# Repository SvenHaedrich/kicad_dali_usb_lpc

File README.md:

KiCad Project for DALI to USB interface based on NXP LPC 1114 µController.

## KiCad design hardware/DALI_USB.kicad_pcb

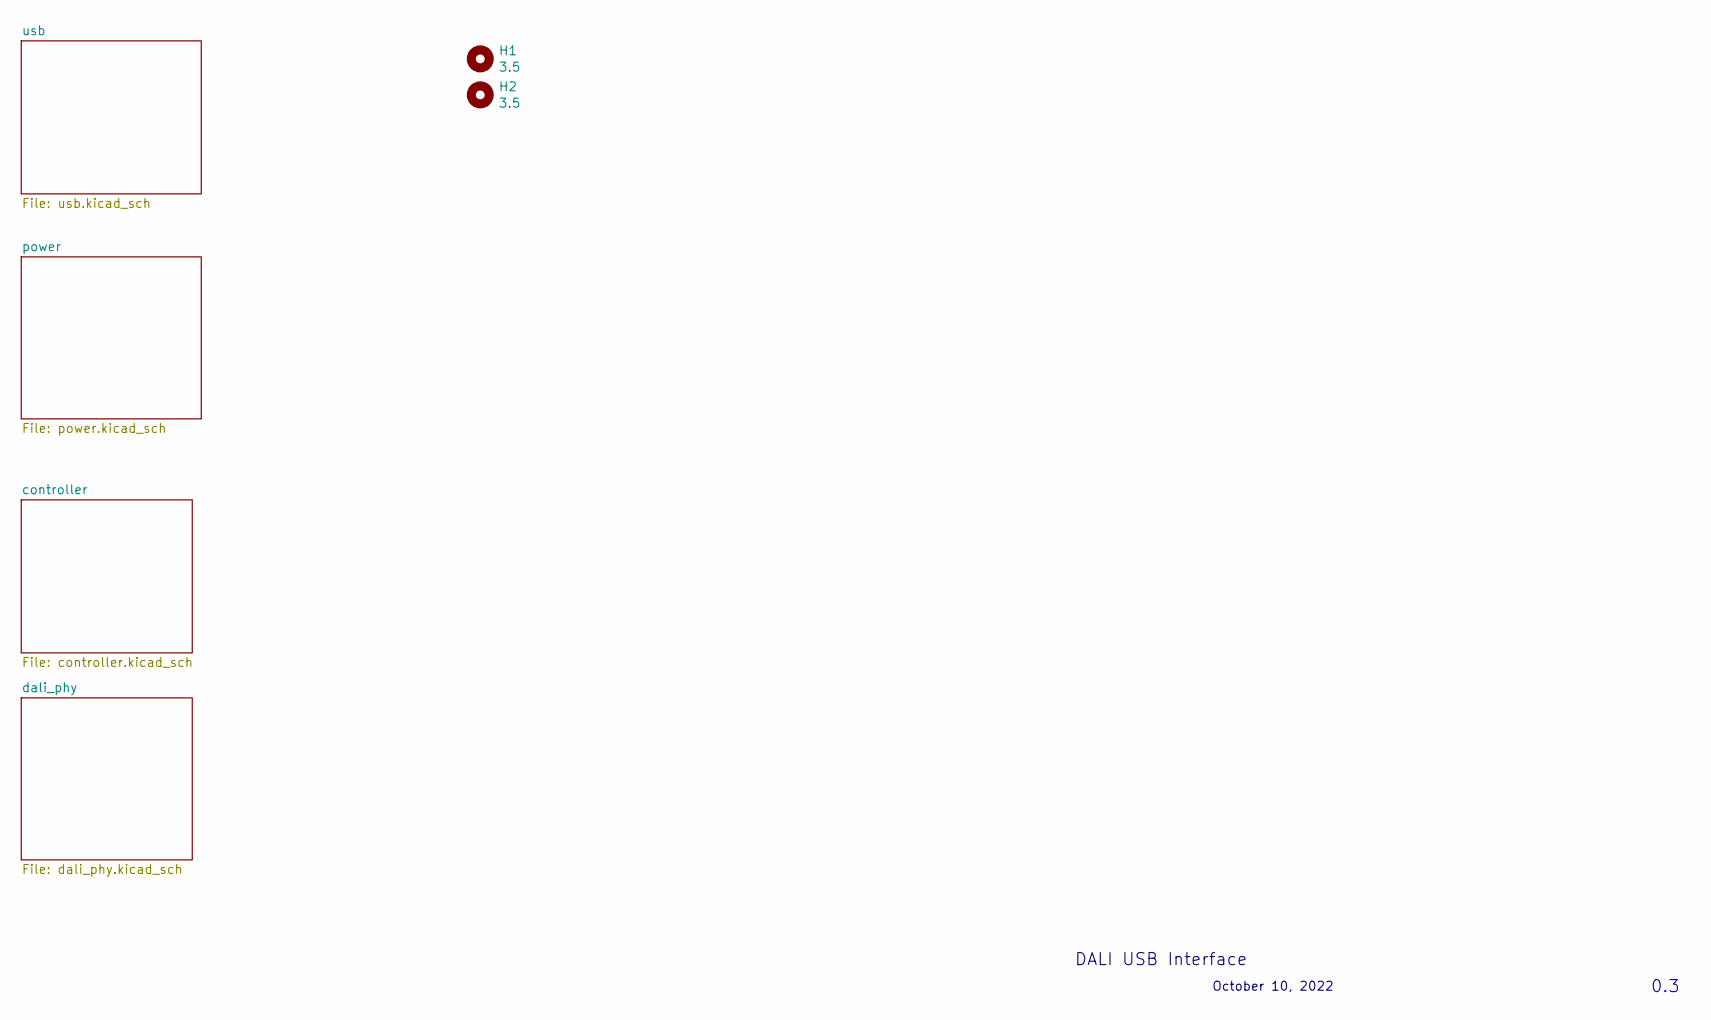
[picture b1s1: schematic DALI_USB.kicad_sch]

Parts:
H1, H2: 3.5; MountingHole_3.5mm

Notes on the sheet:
DALI USB Interface
October 10, 2022
0.3

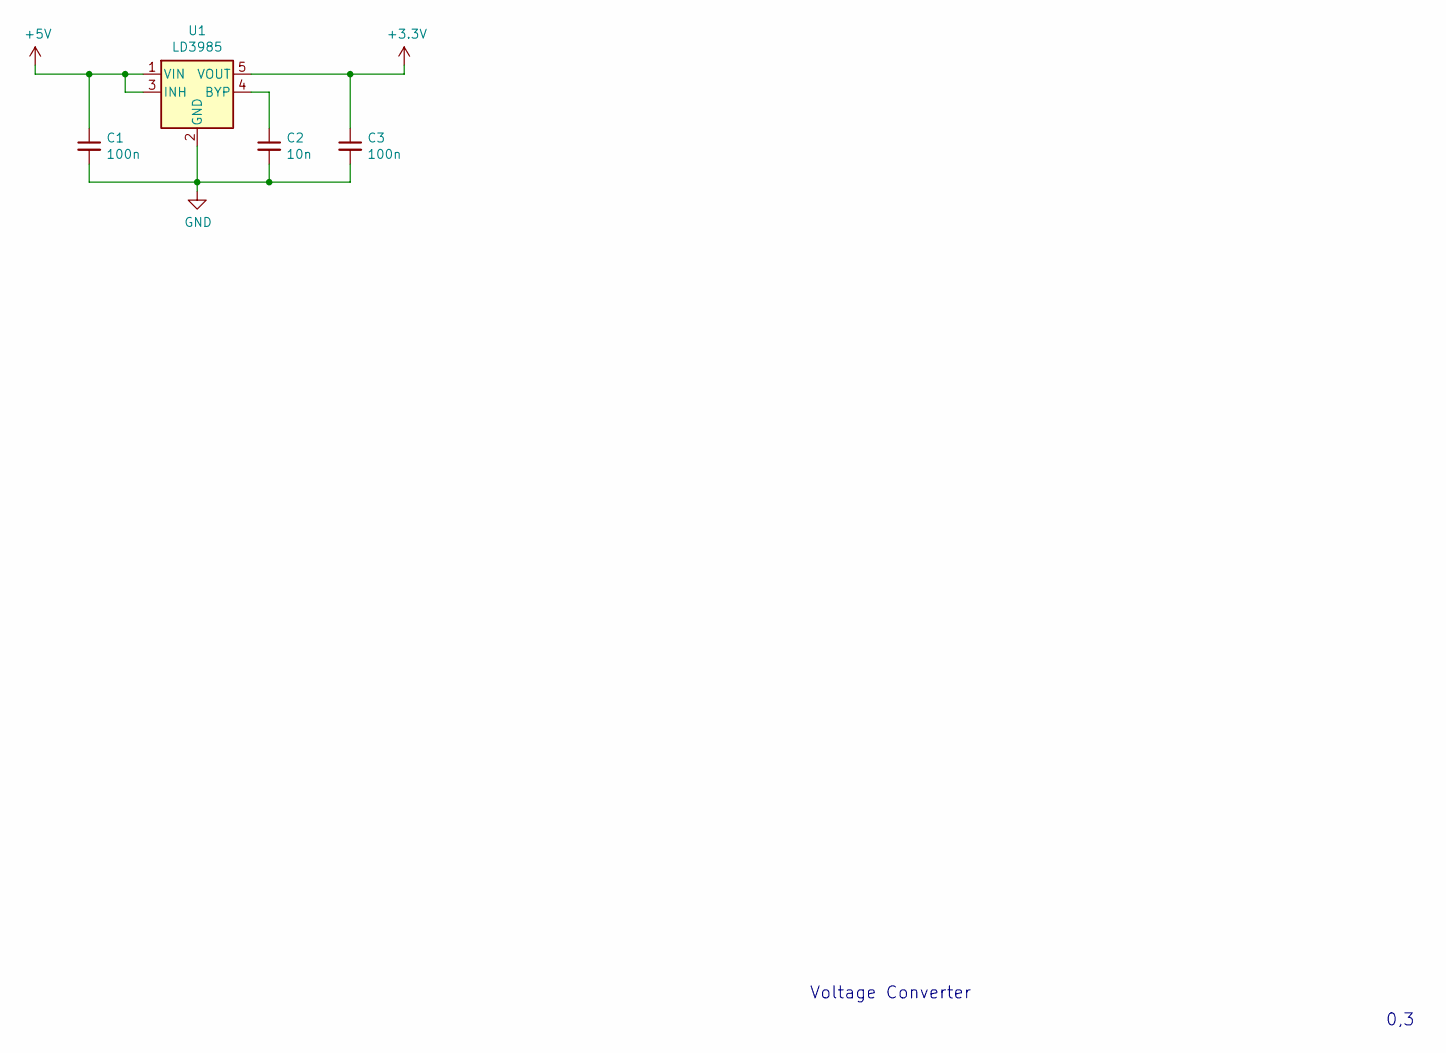
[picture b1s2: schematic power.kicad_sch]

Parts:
C1, C3: 100n; C_0603_1608Metric; LCSC C14663
C2: 10n; C_0603_1608Metric; LCSC C57112
U1: LD3985; SOT-23-5; Digikey 497-3504-1-ND

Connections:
+3V3: C3.1, U1.5 (VOUT); also elsewhere on the board
+5V: C1.1, U1.1 (VIN), U1.3 (INH); also elsewhere on the board
GND: C1.2, C2.2, C3.2, U1.2 (GND); also elsewhere on the board
unnamed: C2.1, U1.4 (BYP)

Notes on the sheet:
0,3
Voltage Converter

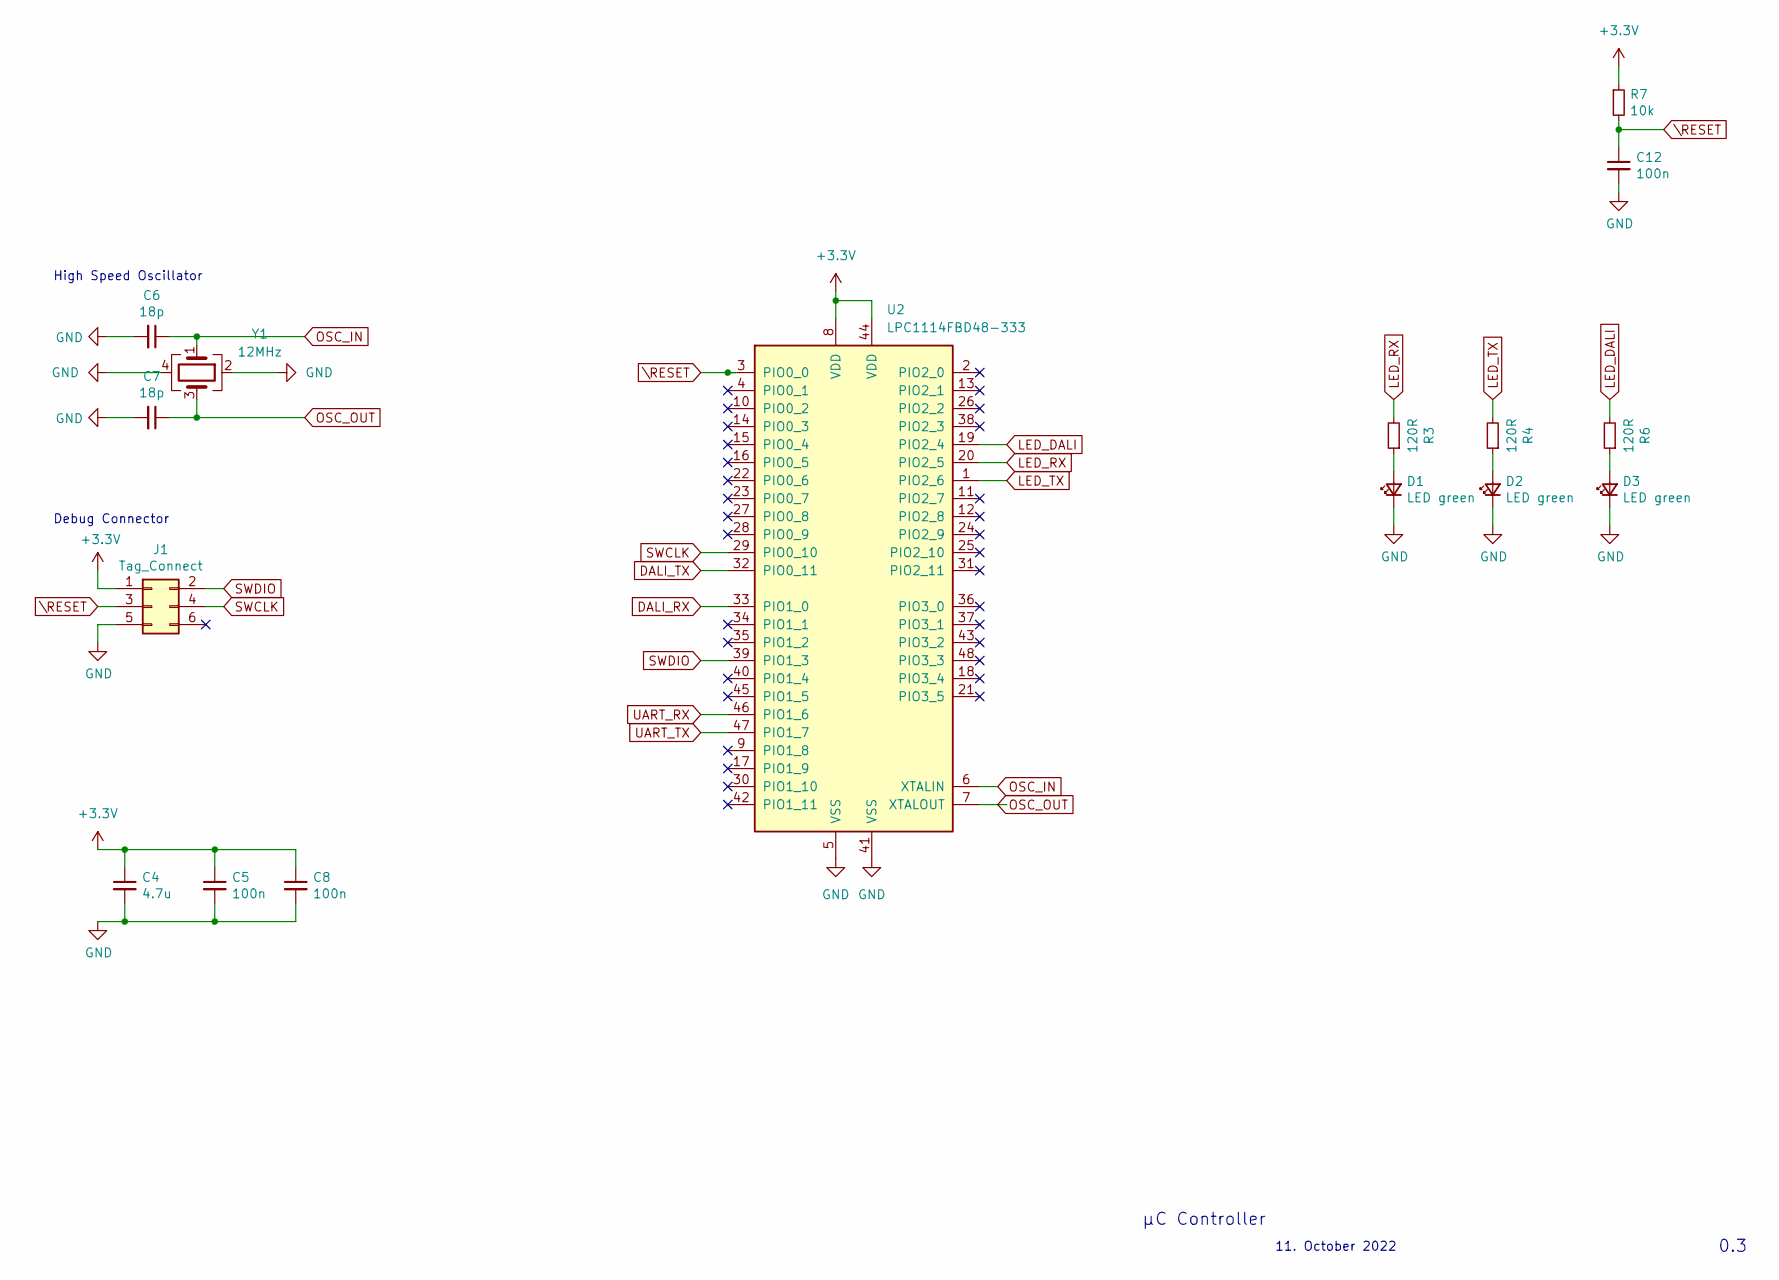
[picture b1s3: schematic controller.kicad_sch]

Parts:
C4: 4.7u; C_0603_1608Metric; LCSC C19666
C5, C8, C12: 100n; C_0603_1608Metric; LCSC C14663
C6, C7: 18p; C_0603_1608Metric; LCSC C38523
D1, D2, D3: LED green; LED_0805_2012Metric; LCSC C98221
J1: Tag_Connect; Tag-Connect_TC2030-IDC-NL_2x03_P1.27mm_Vertical
R3, R4, R6: 120R; R_0603_1608Metric; LCSC C114640
R7: 10k; R_0603_1608Metric; LCSC C25804
U2: LPC1114FBD48-333; LQFP-48_7x7mm_P0.5mm; LCSC C9872
Y1: 12MHz; Crystal_SMD_TXC_7M-4Pin_3.2x2.5mm; LCSC C9002

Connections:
+3V3: C4.1, C5.1, C8.1, J1.1, R7.1, U2.8 (VDD), U2.44 (VDD); also elsewhere on the board
DALI_RX: U2.33 (PIO1_0); also elsewhere on the board
DALI_TX: U2.32 (PIO0_11); also elsewhere on the board
GND: C4.2, C5.2, C6.2, C7.2, C8.2, C12.2, D1.1 (K), D2.1 (K), D3.1 (K), J1.5, U2.5 (VSS), U2.41 (VSS), Y1.2, Y1.4; also elsewhere on the board
LED_DALI: R6.2, U2.19 (PIO2_4)
LED_RX: R3.2, U2.20 (PIO2_5)
LED_TX: R4.2, U2.1 (PIO2_6)
unnamed: D1.2 (A), R3.1
unnamed: D2.2 (A), R4.1
unnamed: D3.2 (A), R6.1
OSC_IN: C6.1, U2.6 (XTALIN), Y1.1
OSC_OUT: C7.1, U2.7 (XTALOUT), Y1.3
SWCLK: J1.4, U2.29 (PIO0_10)
SWDIO: J1.2, U2.39 (PIO1_3)
UART_RX: U2.46 (PIO1_6); also elsewhere on the board
UART_TX: U2.47 (PIO1_7); also elsewhere on the board
\RESET: C12.1, J1.3, R7.2, U2.3 (PIO0_0)

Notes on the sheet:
Debug Connector
11. October 2022
High Speed Oscillator
µC Controller
0.3

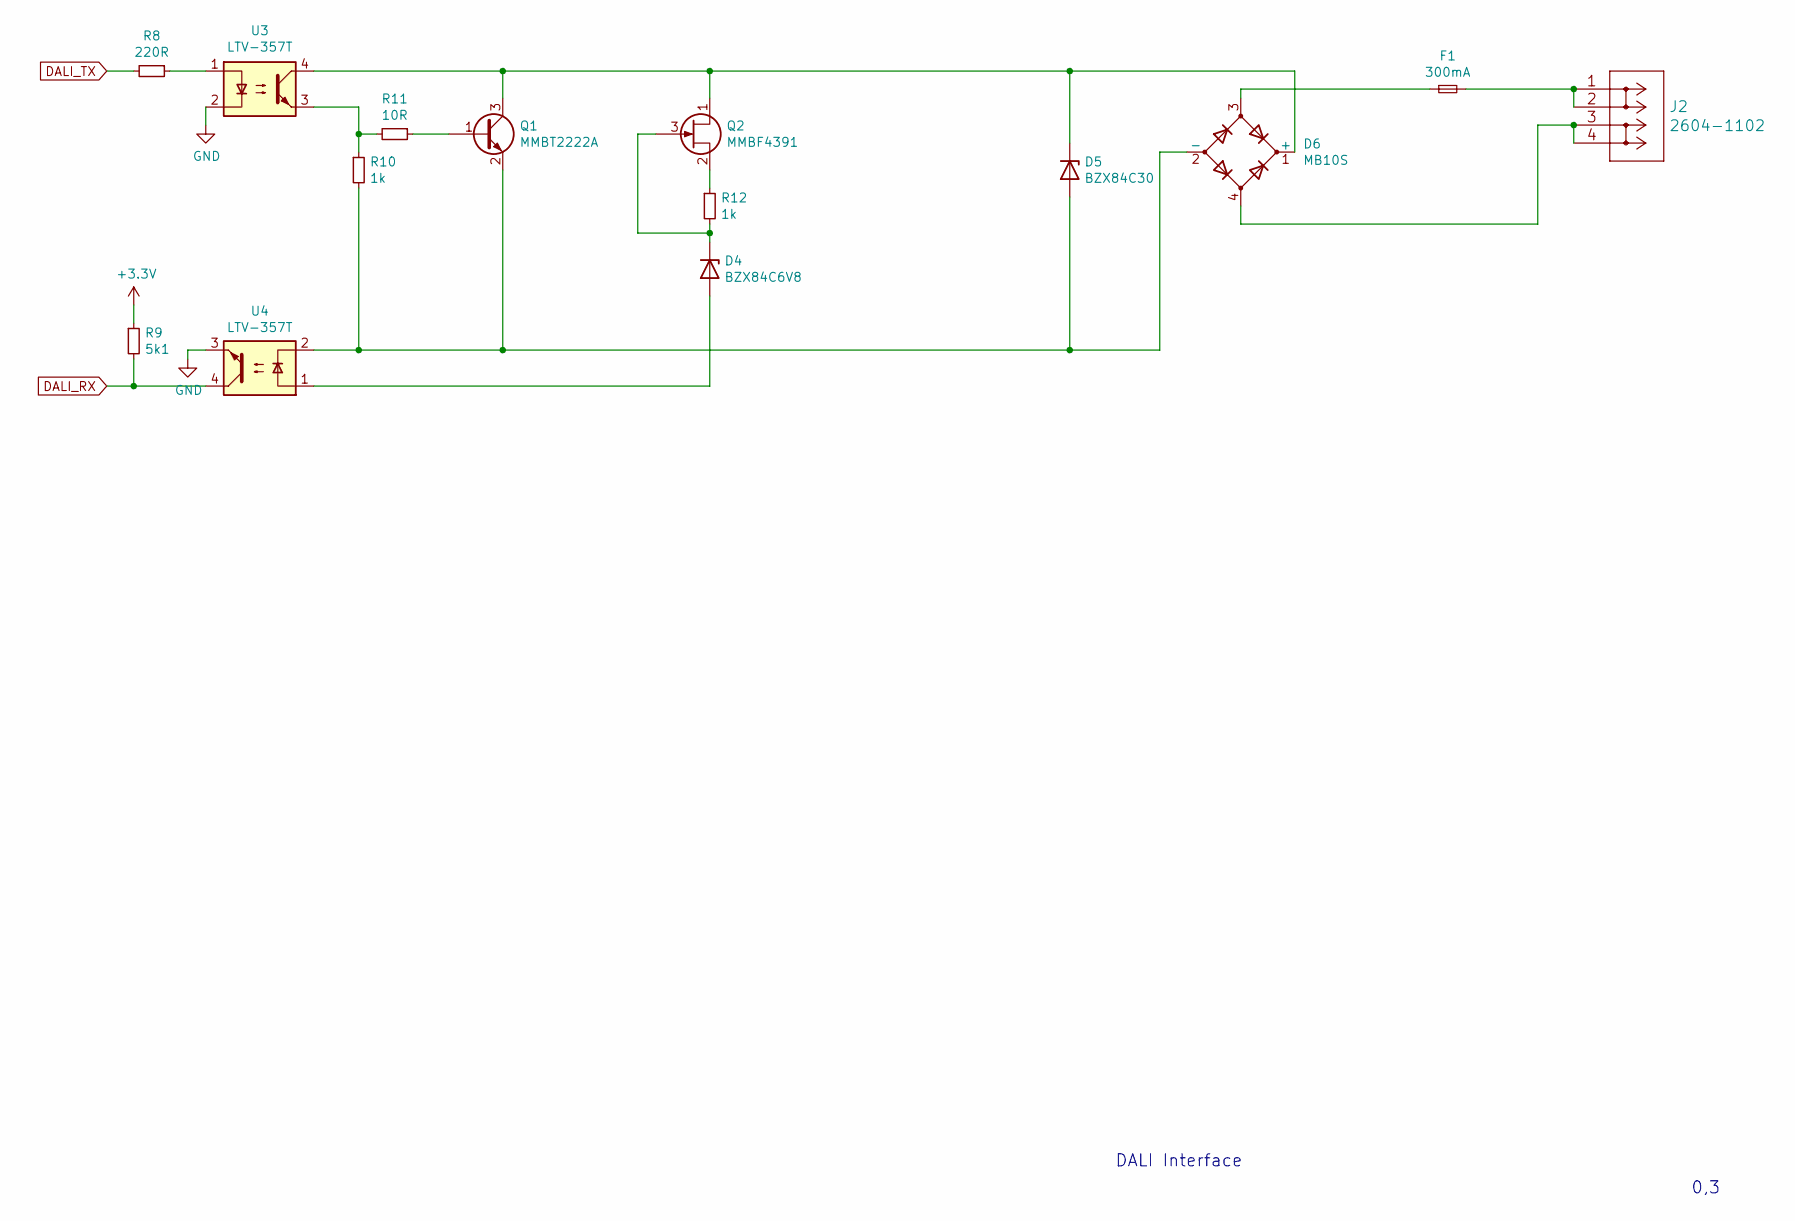
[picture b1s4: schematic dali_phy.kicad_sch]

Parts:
D4: BZX84C6V8; D_SOT-23_ANK; Digikey BZX84C3V9FSCT-ND
D5: BZX84C30; D_SOT-23_ANK; Digikey 112-BZX84C30-E3-08CT-ND
D6: MB10S; TO-269AA; Digikey MB4SCT-ND
F1: 300mA; Fuse_1210_3225Metric; LCSC C70086
J2: 2604-1102
Q1: MMBT2222A; SOT-23; Digikey MMBT5550LT3G
Q2: MMBF4391; SOT-23; LCSC C153770
R8: 220R; R_0603_1608Metric; LCSC C22962
R9: 5k1; R_0603_1608Metric; LCSC C365441
R10, R12: 1k; R_0603_1608Metric; LCSC C21190
R11: 10R; R_0603_1608Metric; LCSC C22859
U3, U4: LTV-357T; SO-4_4.4x3.6mm_P2.54mm; Digikey LTV-357T

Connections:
+3V3: R9.1; also elsewhere on the board
DALI_RX: R9.2, U4.4; also elsewhere on the board
DALI_TX: R8.2; also elsewhere on the board
GND: U3.2, U4.3; also elsewhere on the board
unnamed: D4.1 (K), Q2.3 (G), R12.2
unnamed: D4.2 (A), U4.1
unnamed: D5.1 (K), D6.1 (+), Q1.3 (C), Q2.1 (D), U3.4
unnamed: D5.2 (A), D6.2 (-), Q1.2 (E), R10.2, U4.2
unnamed: D6.3, F1.1
unnamed: D6.4, J2.3, J2.4
unnamed: F1.2, J2.1, J2.2
unnamed: Q1.1 (B), R11.1
unnamed: Q2.2 (S), R12.1
unnamed: R8.1, U3.1
unnamed: R10.1, R11.2, U3.3

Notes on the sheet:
DALI Interface
0,3

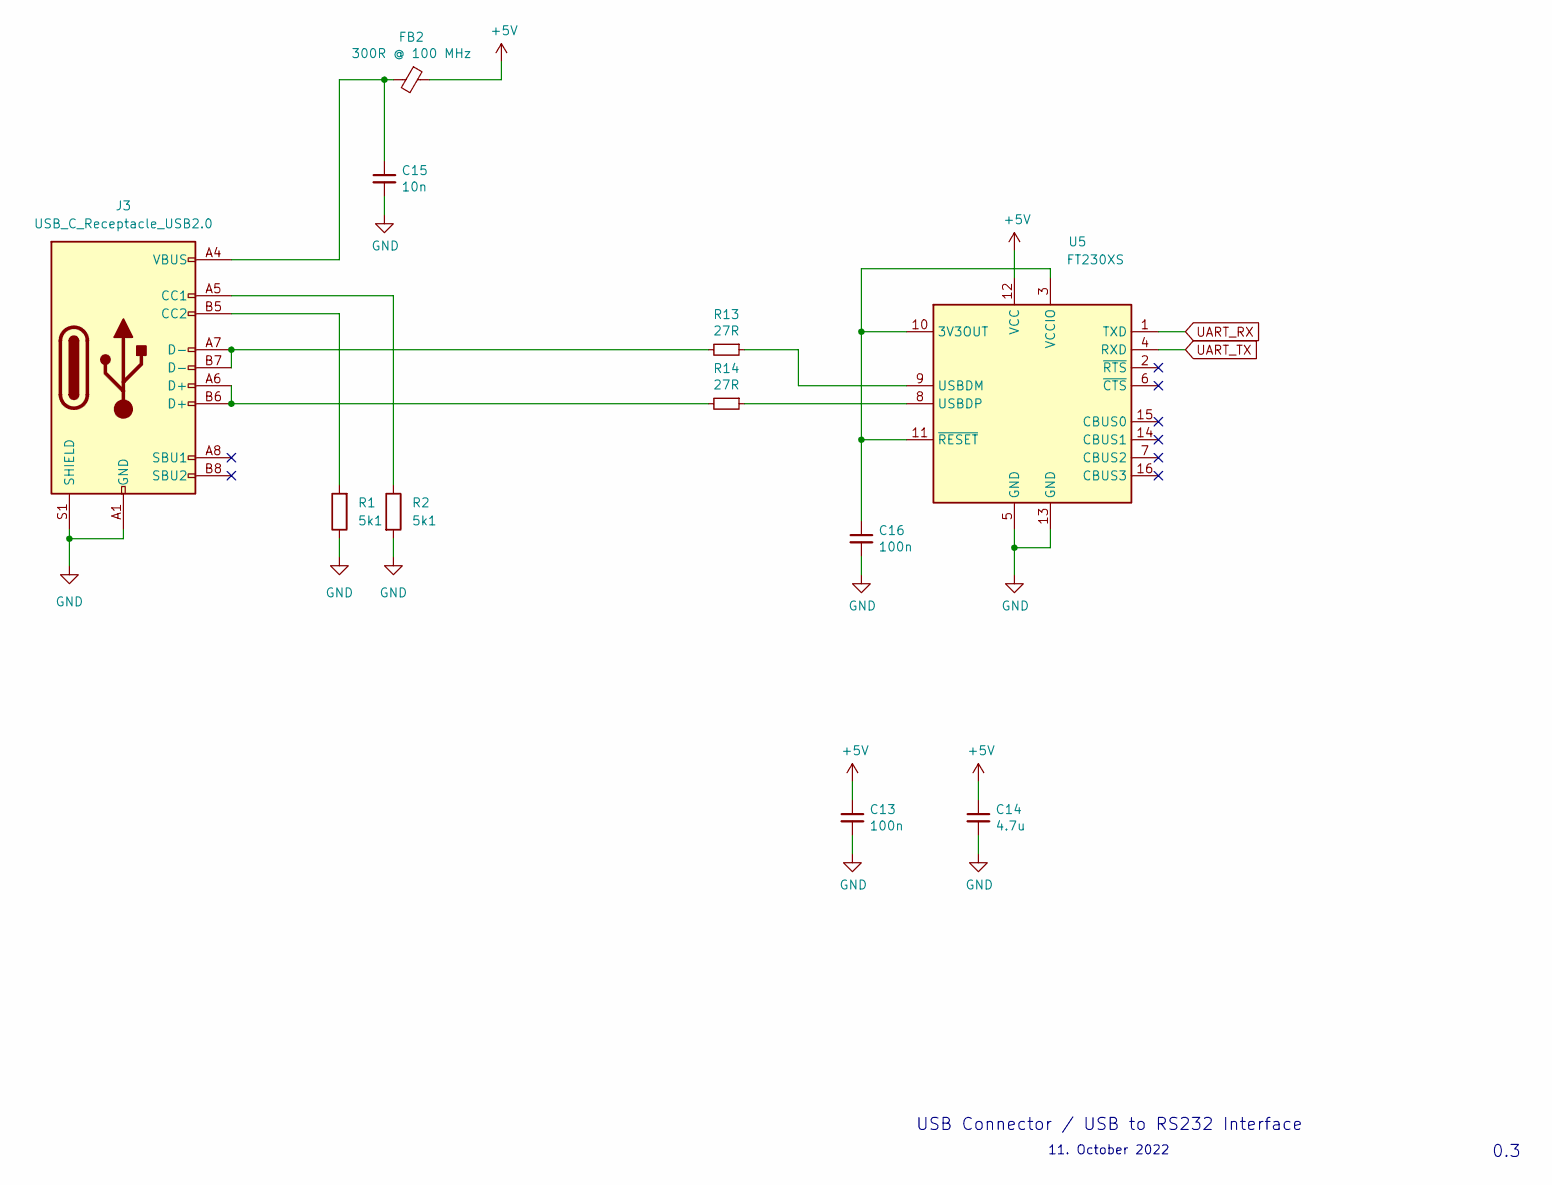
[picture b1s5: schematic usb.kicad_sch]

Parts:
C13, C16: 100n; C_0603_1608Metric; LCSC C14663
C14: 4.7u; C_0603_1608Metric; LCSC C19666
C15: 10n; C_0603_1608Metric; LCSC C57112
FB2: 300R @ 100 MHz; R_0603_1608Metric; Digikey LBR29012T100M
J3: USB_C_Receptacle_USB2.0; USB_C_Receptacle_XKB_U262-16XN-4BVC11; LCSC C2987386
R1, R2: 5k1; R_0603_1608Metric; LCSC C365441
R13, R14: 27R; R_0603_1608Metric; LCSC C25190
U5: FT230XS; SSOP-16_3.9x4.9mm_P0.635mm; Digikey 768-1135-6-ND

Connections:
+5V: C13.1, C14.1, FB2.1, U5.12 (VCC); also elsewhere on the board
GND: C13.2, C14.2, C15.2, C16.2, J3.A1 (GND), J3.A12 (GND), J3.B1 (GND), J3.B12 (GND), J3.S1 (SHIELD), R1.1, R2.2, U5.5 (GND), U5.13 (GND); also elsewhere on the board
unnamed: C15.1, FB2.2, J3.A4 (VBUS), J3.A9 (VBUS), J3.B4 (VBUS), J3.B9 (VBUS)
unnamed: C16.1, U5.3 (VCCIO), U5.10 (3V3OUT), U5.11 (~RESET)
unnamed: J3.A5 (CC1), R2.1
unnamed: J3.B5 (CC2), R1.2
unnamed: J3.A7 (D-), J3.B7 (D-), R13.2
unnamed: J3.A6 (D+), J3.B6 (D+), R14.2
unnamed: R14.1, U5.8 (USBDP)
unnamed: R13.1, U5.9 (USBDM)
UART_RX: U5.1 (TXD); also elsewhere on the board
UART_TX: U5.4 (RXD); also elsewhere on the board

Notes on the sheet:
11. October 2022
USB Connector / USB to RS232 Interface
0.3

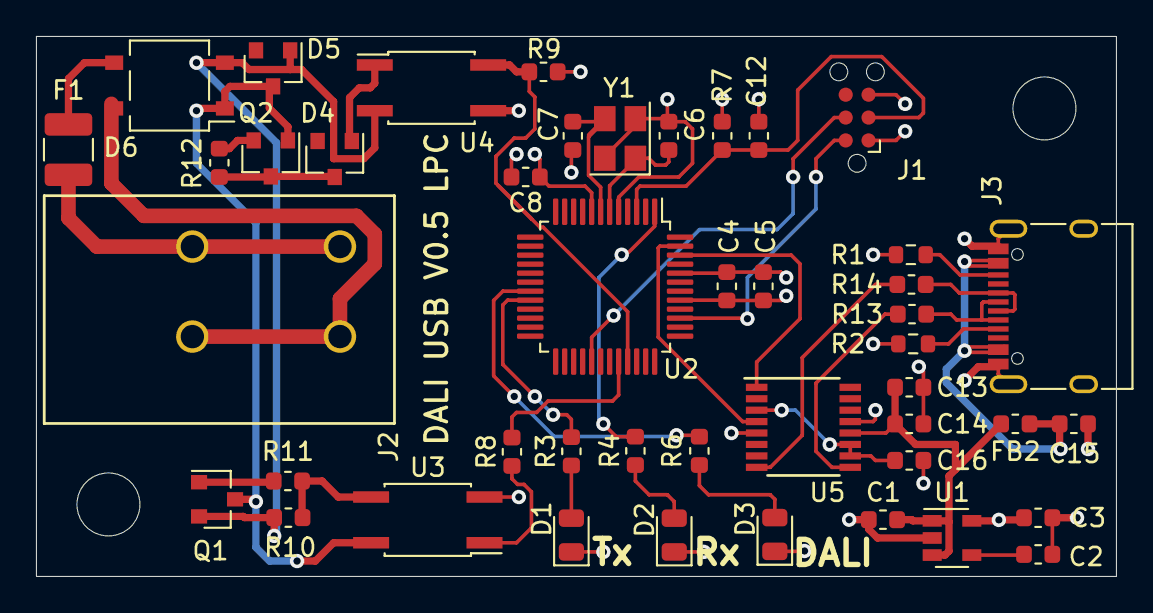
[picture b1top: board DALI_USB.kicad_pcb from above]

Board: 4 copper layers, 60.0 x 30.0 mm, 47 parts (0 on the bottom side), 38 nets.

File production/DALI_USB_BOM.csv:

Comment,Designator,Footprint,LCSC
"100n","C1,C3,C5,C8,C12,C13,C16","Capacitor_SMD:C_0603_1608Metric","C14663"
"4.7u","C4,C14","Capacitor_SMD:C_0603_1608Metric","C19666"
"10n","C2,C15","Capacitor_SMD:C_0603_1608Metric","C57112"
"18p","C6,C7","Capacitor_SMD:C_0603_1608Metric","C38523"
"LED green","D1,D2,D3","LED_SMD:LED_0805_2012Metric","C98221"
"BZX84C6V8","D4","Diode_SMD:D_SOT-23_ANK","C90848 "
"BZX84C30","D5","Diode_SMD:D_SOT-23_ANK","C118586"
"MB10S","D6","Package_TO_SOT_SMD:TO-269AA","C2488"
"300mA","F1","Fuse:Fuse_1210_3225Metric","C70086"
"300R @ 100 MHz","FB2","Resistor_SMD:R_0603_1608Metric","C96698"
"3.5","H1,H2","MountingHole:MountingHole_3.5mm",""
"Tag_Connect","J1","Connector:Tag-Connect_TC2030-IDC-NL_2x03_P1.27mm_Vertical",""
"2604-1102","J2","DALI_USB V0:2604-1102",""
"USB_C_Receptacle_USB2.0","J3","Connector_USB:USB_C_Receptacle_XKB_U262-16XN-4BVC11","C2987386"
"MMBT2222A","Q1","Package_TO_SOT_SMD:SOT-23","C83939"
"MMBF4391","Q2","Package_TO_SOT_SMD:SOT-23","C153770"
"5k1","R1,R2,R9","Resistor_SMD:R_0603_1608Metric","C365441"
"1k","R10,R12","Resistor_SMD:R_0603_1608Metric","C21190"
"10R","R11","Resistor_SMD:R_0603_1608Metric","C22859"
"27R","R13,R14","Resistor_SMD:R_0603_1608Metric","C25190"
"120R","R3,R4,R6","Resistor_SMD:R_0603_1608Metric","C114640"
"10k","R7","Resistor_SMD:R_0603_1608Metric","C25804"
"220R","R8","Resistor_SMD:R_0603_1608Metric","C22962"
"LD3985","U1","Package_TO_SOT_SMD:SOT-23-5","C157416"
"LPC1114FBD48-333","U2","Package_QFP:LQFP-48_7x7mm_P0.5mm","C9872"
"LTV-357T","U3,U4","Package_SO:SO-4_4.4x3.6mm_P2.54mm","C33068"
"FT230XS","U5","Package_SO:SSOP-16_3.9x4.9mm_P0.635mm","C69082"
"12MHz","Y1","Crystal:Crystal_SMD_TXC_7M-4Pin_3.2x2.5mm","C9002"

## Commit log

2022-10-16 second commit
2022-10-16 change path for datasheets
2022-10-16 move 3d files
2022-10-16 fix 3d models
2022-10-16 add a 3D view
2022-10-16 add 3D view of pcb
2023-04-04 minor changes, add a picture of finished hardware
2023-04-04 add a real picture of the finish product
2024-08-04 add license file to project

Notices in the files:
parts and their libraries:
Copyright 2016 Accelerated Designs. All rights reserved.
